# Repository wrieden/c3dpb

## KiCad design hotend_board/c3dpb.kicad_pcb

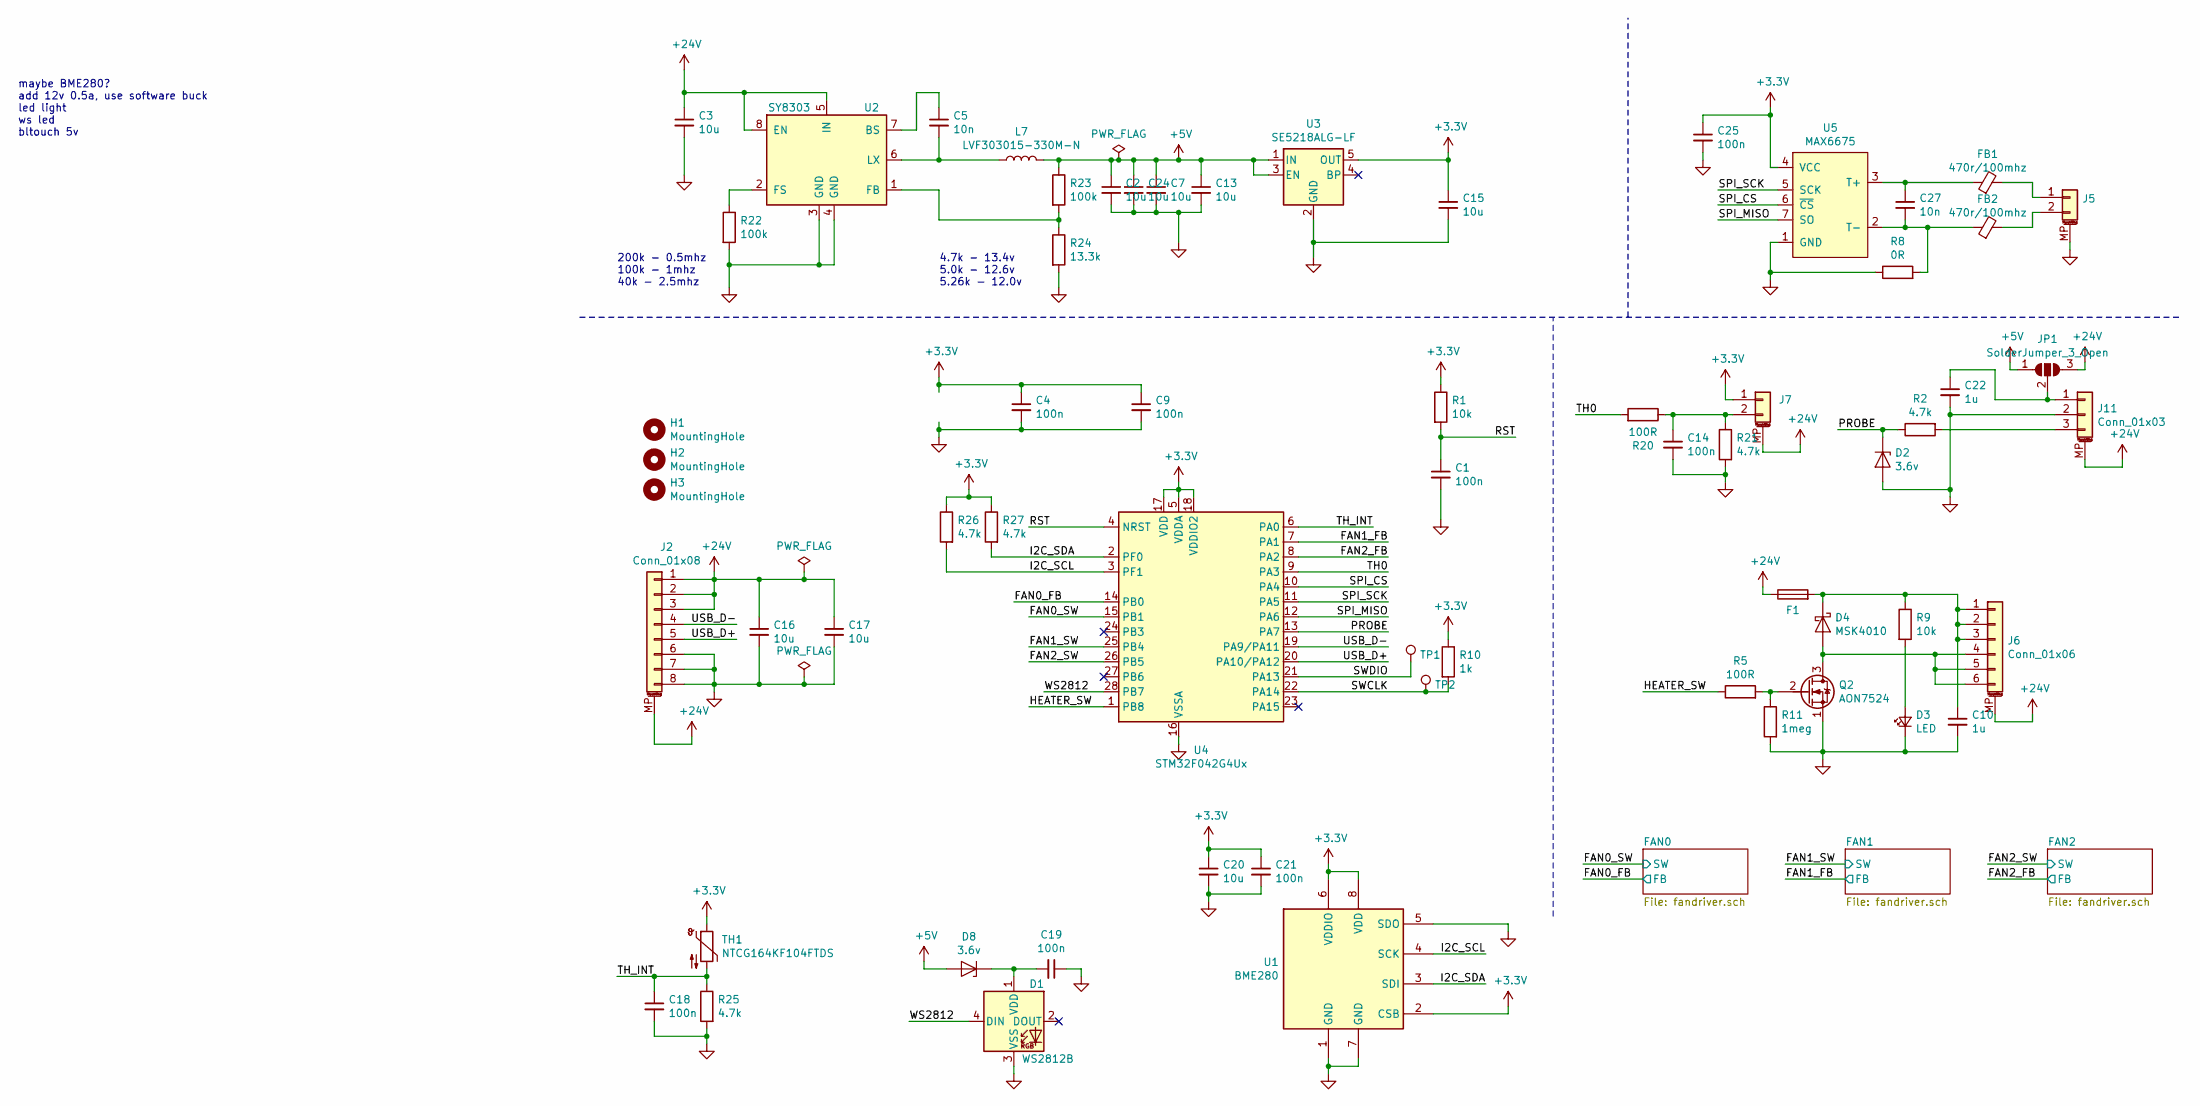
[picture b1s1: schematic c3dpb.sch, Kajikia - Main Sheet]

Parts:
C1, C4, C9, C14, C18, C19, C21, C25: 100n; 0603_CAP
C2, C7, C13, C15, C20, C24: 10u; 0603_CAP
C3, C16, C17: 10u; 1210_CAP
C5, C27: 10n; 0603_CAP
C10, C22: 1u; 0603_CAP
D1: WS2812B; WS2812B-MINI
D2, D8: 3.6v; 0603_DIODE
D3: LED; 0603_LED
D4: MSK4010; SOD-523_DIODE
F1: Fuse; 1206_RES
FB1, FB2: 470r/100mhz; 0603_IND
H1, H2: MountingHole; MountingHole_2.2mm_M2_ISO7380
H3: MountingHole; MountingHole_4.3mm_M4_ISO14580
J2: Conn_01x08; JST_SH_BM08B-SRSS-TB_1x08-1MP_P1.00mm_Vertical
J5, J7: Conn_01x02; JST_SH_BM02B-SRSS-TB_1x02-1MP_P1.00mm_Vertical
J6: Conn_01x06; JST_SH_BM06B-SRSS-TB_1x06-1MP_P1.00mm_Vertical
J11: Conn_01x03; JST_SH_BM03B-SRSS-TB_1x03-1MP_P1.00mm_Vertical
JP1: SolderJumper_3_Open; Solder Jumper 3P
L7: LVF303015-330M-N; 3x3mm_IND
Q2: AON7524; DFN3x3A_8L_EP1_P
R1, R9: 10k; 0603_RES
R2, R21, R25, R26, R27: 4.7k; 0603_RES
R5, R20: 100R; 0603_RES
R8: 0R; 0603_RES
R10: 1k; 0603_RES
R11: 1meg; 0603_RES
R22, R23: 100k; 0603_RES
R24: 13.3k; 0603_RES
TH1: NTCG164KF104FTDS; 0603_RES
TP1, TP2: TestPoint; TestPoint_Pad_D1.0mm
U1: BME280; Bosch_LGA-8_2.5x2.5mm_P0.65mm_ClockwisePinNumbering
U2: SY8303; TSOT-23-8
U3: SE5218ALG-LF; SOT-23-5
U4: STM32F042G4Ux; QFN-28_4x4mm_P0.5mm
U5: MAX6675; SO-8

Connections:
+3V3: C4.1, C9.1, C15.1, C20.1, C21.1, C25.1, J7.1, R1.1, R10.1, R26.1, R27.1, TH1.1, U1.2 (CSB), U1.6 (VDDIO), U1.8 (VDD), U3.5 (OUT), U4.5 (VDDA), U4.17 (VDD), U4.18 (VDDIO2), U5.4 (VCC)
+5V: C2.1, C7.1, C13.1, C24.1, D8.2 (A), JP1.1 (A), L7.2, R23.1, U3.1 (IN), U3.3 (EN)
+24V: C3.1, C16.1, C17.1, F1.1, J2.1, J2.2, J2.3, J2.MP (MountPin), J6.MP (MountPin), J7.MP (MountPin), J11.MP (MountPin), JP1.3 (B), U2.5 (IN), U2.8 (EN); also elsewhere on the board
/FAN0_FB: U4.14 (PB0); also elsewhere on the board
/FAN0_SW: U4.15 (PB1); also elsewhere on the board
/FAN1_FB: U4.7 (PA1); also elsewhere on the board
/FAN1_SW: U4.25 (PB4); also elsewhere on the board
/FAN2_FB: U4.8 (PA2); also elsewhere on the board
/FAN2_SW: U4.26 (PB5); also elsewhere on the board
/HEATER_SW: R5.1, U4.1 (PB8)
/I2C_SCL: R26.2, U1.4 (SCK), U4.3 (PF1)
/I2C_SDA: R27.2, U1.3 (SDI), U4.2 (PF0)
/PROBE: D2.1 (K), R2.1, U4.13 (PA7)
/RST: C1.1, R1.2, U4.4 (NRST)
/SPI_CS: U4.10 (PA4), U5.6 (~CS)
/SPI_MISO: U4.12 (PA6), U5.7 (SO)
/SPI_SCK: U4.11 (PA5), U5.5 (SCK)
/SWCLK: R10.2, TP2.1, U4.22 (PA14)
/SWDIO: TP1.1, U4.21 (PA13)
/TH0: R20.2, U4.9 (PA3)
/TH_INT: C18.1, R25.1, TH1.2, U4.6 (PA0)
/USB_D+: J2.5, U4.20 (PA10/PA12)
/USB_D-: J2.4, U4.19 (PA9/PA11)
/WS2812: D1.4 (DIN), U4.28 (PB7)
GND: C1.2, C2.2, C3.2, C4.2, C7.2, C9.2, C10.2, C13.2, C14.2, C15.2, C16.2, C17.2, C18.2, C19.1, C20.2, C21.2, C22.2, C24.2, C25.2, D1.3 (VSS), D2.2 (A), D3.1 (K), J2.6, J2.7, J2.8, J5.MP (MountPin), J11.2, Q2.1 (S), R8.1, R11.2, R21.2, R22.2, R24.2, R25.2, U1.1 (GND), U1.5 (SDO), U1.7 (GND), U2.3 (GND), U2.4 (GND), U3.2 (GND), U4.16 (VSSA), U5.1 (GND); also elsewhere on the board
unnamed: C5.1, U2.7 (BS)
unnamed: C5.2, L7.1, U2.6 (LX)
unnamed: C10.1, D4.1 (K), F1.2, J6.1, J6.2, J6.3, R9.1
unnamed: C14.1, J7.2, R20.1, R21.1
unnamed: C19.2, D1.1 (VDD), D8.1 (K)
unnamed: C22.1, J11.1, JP1.2 (C)
unnamed: C27.1, FB1.1, U5.3 (T+)
unnamed: C27.2, FB2.1, R8.2, U5.2 (T-)
unnamed: D3.2 (A), R9.2
unnamed: D4.2 (A), J6.4, J6.5, J6.6, Q2.3 (D)
unnamed: FB1.2, J5.1
unnamed: FB2.2, J5.2
unnamed: J11.3, R2.2
unnamed: Q2.2 (G), R5.2, R11.1
unnamed: R22.1, U2.2 (FS)
unnamed: R23.2, R24.1, U2.1 (FB)

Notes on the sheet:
maybe BME280? add 12v 0.5a, use software buck led light ws led bltouch 5v
4.7k - 13.4v 5.0k - 12.6v 5.26k - 12.0v
200k - 0.5mhz 100k - 1mhz 40k - 2.5mhz

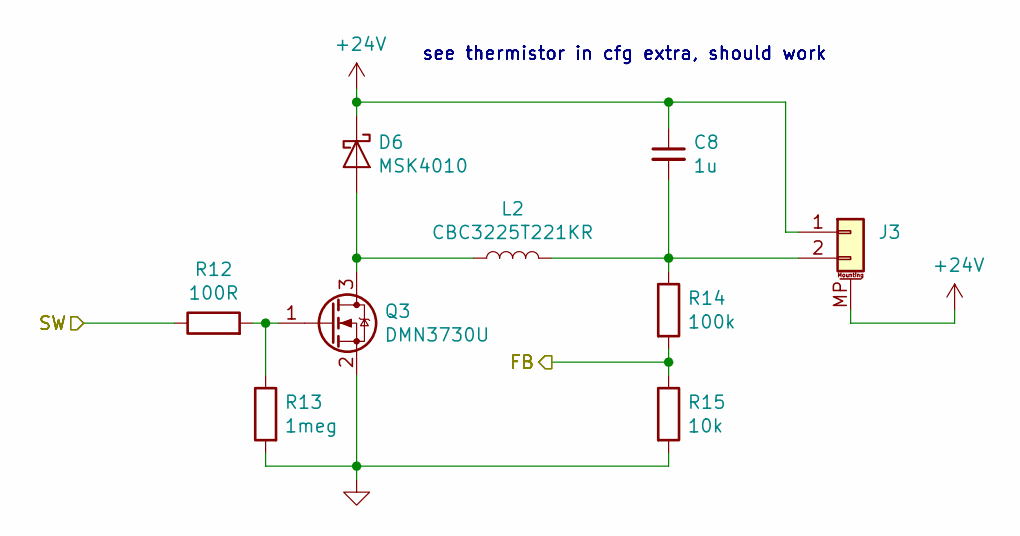
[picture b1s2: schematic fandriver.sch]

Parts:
C6: 1u; 0603_CAP
D5: MSK4010; SOD-523_DIODE
J1: Conn_01x02; JST_SH_BM02B-SRSS-TB_1x02-1MP_P1.00mm_Vertical
L1: CBC3225T221KR; 1210_CAP
Q1: DMN3730U; SOT-23
R3: 100R; 0603_RES
R4: 1meg; 0603_RES
R6: 100k; 0603_RES
R7: 10k; 0603_RES

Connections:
+24V: C6.1, D5.1 (K), J1.1, J1.MP (MountPin); also elsewhere on the board
/FAN0_FB: R6.2, R7.1; also elsewhere on the board
/FAN0_SW: R3.1; also elsewhere on the board
GND: Q1.2 (S), R4.2, R7.2; also elsewhere on the board
unnamed: C6.2, J1.2, L1.2, R6.1
unnamed: D5.2 (A), L1.1, Q1.3 (D)
unnamed: Q1.1 (G), R3.2, R4.1

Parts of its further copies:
C8, C11: 1u; 0603_CAP
D6, D7: MSK4010; SOD-523_DIODE
J3, J4: Conn_01x02; JST_SH_BM02B-SRSS-TB_1x02-1MP_P1.00mm_Vertical
L2, L3: CBC3225T221KR; 1210_CAP
Q3, Q4: DMN3730U; SOT-23
R12, R16: 100R; 0603_RES
R13, R17: 1meg; 0603_RES
R14, R18: 100k; 0603_RES
R15, R19: 10k; 0603_RES

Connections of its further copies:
+24V: C8.1, C11.1, D6.1 (K), D7.1 (K), J3.1, J3.MP (MountPin), J4.1, J4.MP (MountPin); also elsewhere on the board
/FAN1_FB: R14.2, R15.1; also elsewhere on the board
/FAN1_SW: R12.1; also elsewhere on the board
/FAN2_FB: R18.2, R19.1; also elsewhere on the board
/FAN2_SW: R16.1; also elsewhere on the board
GND: Q3.2 (S), Q4.2 (S), R13.2, R15.2, R17.2, R19.2; also elsewhere on the board
unnamed: C8.2, J3.2, L2.2, R14.1
unnamed: C11.2, J4.2, L3.2, R18.1
unnamed: D6.2 (A), L2.1, Q3.3 (D)
unnamed: D7.2 (A), L3.1, Q4.3 (D)
unnamed: Q3.1 (G), R12.2, R13.1
unnamed: Q4.1 (G), R16.2, R17.1

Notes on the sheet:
see thermistor in cfg extra, should work

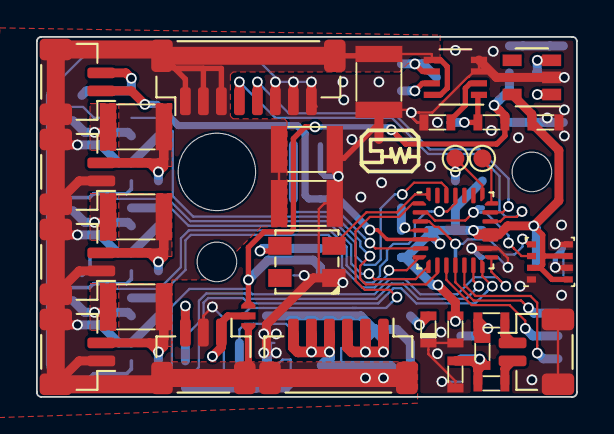
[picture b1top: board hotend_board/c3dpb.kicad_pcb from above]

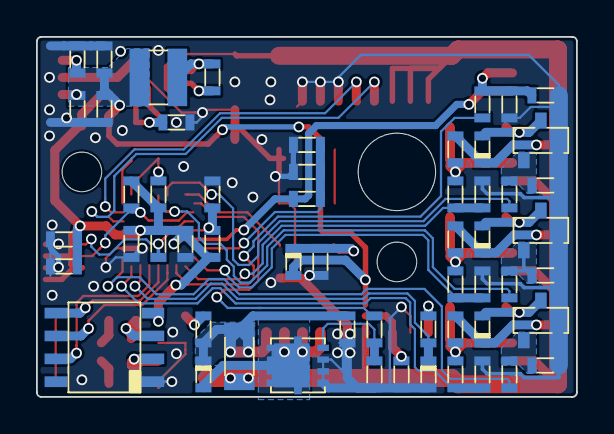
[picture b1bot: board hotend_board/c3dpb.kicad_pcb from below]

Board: 2 copper layers, 30.0 x 20.0 mm, 90 parts (56 on the bottom side), 50 nets.

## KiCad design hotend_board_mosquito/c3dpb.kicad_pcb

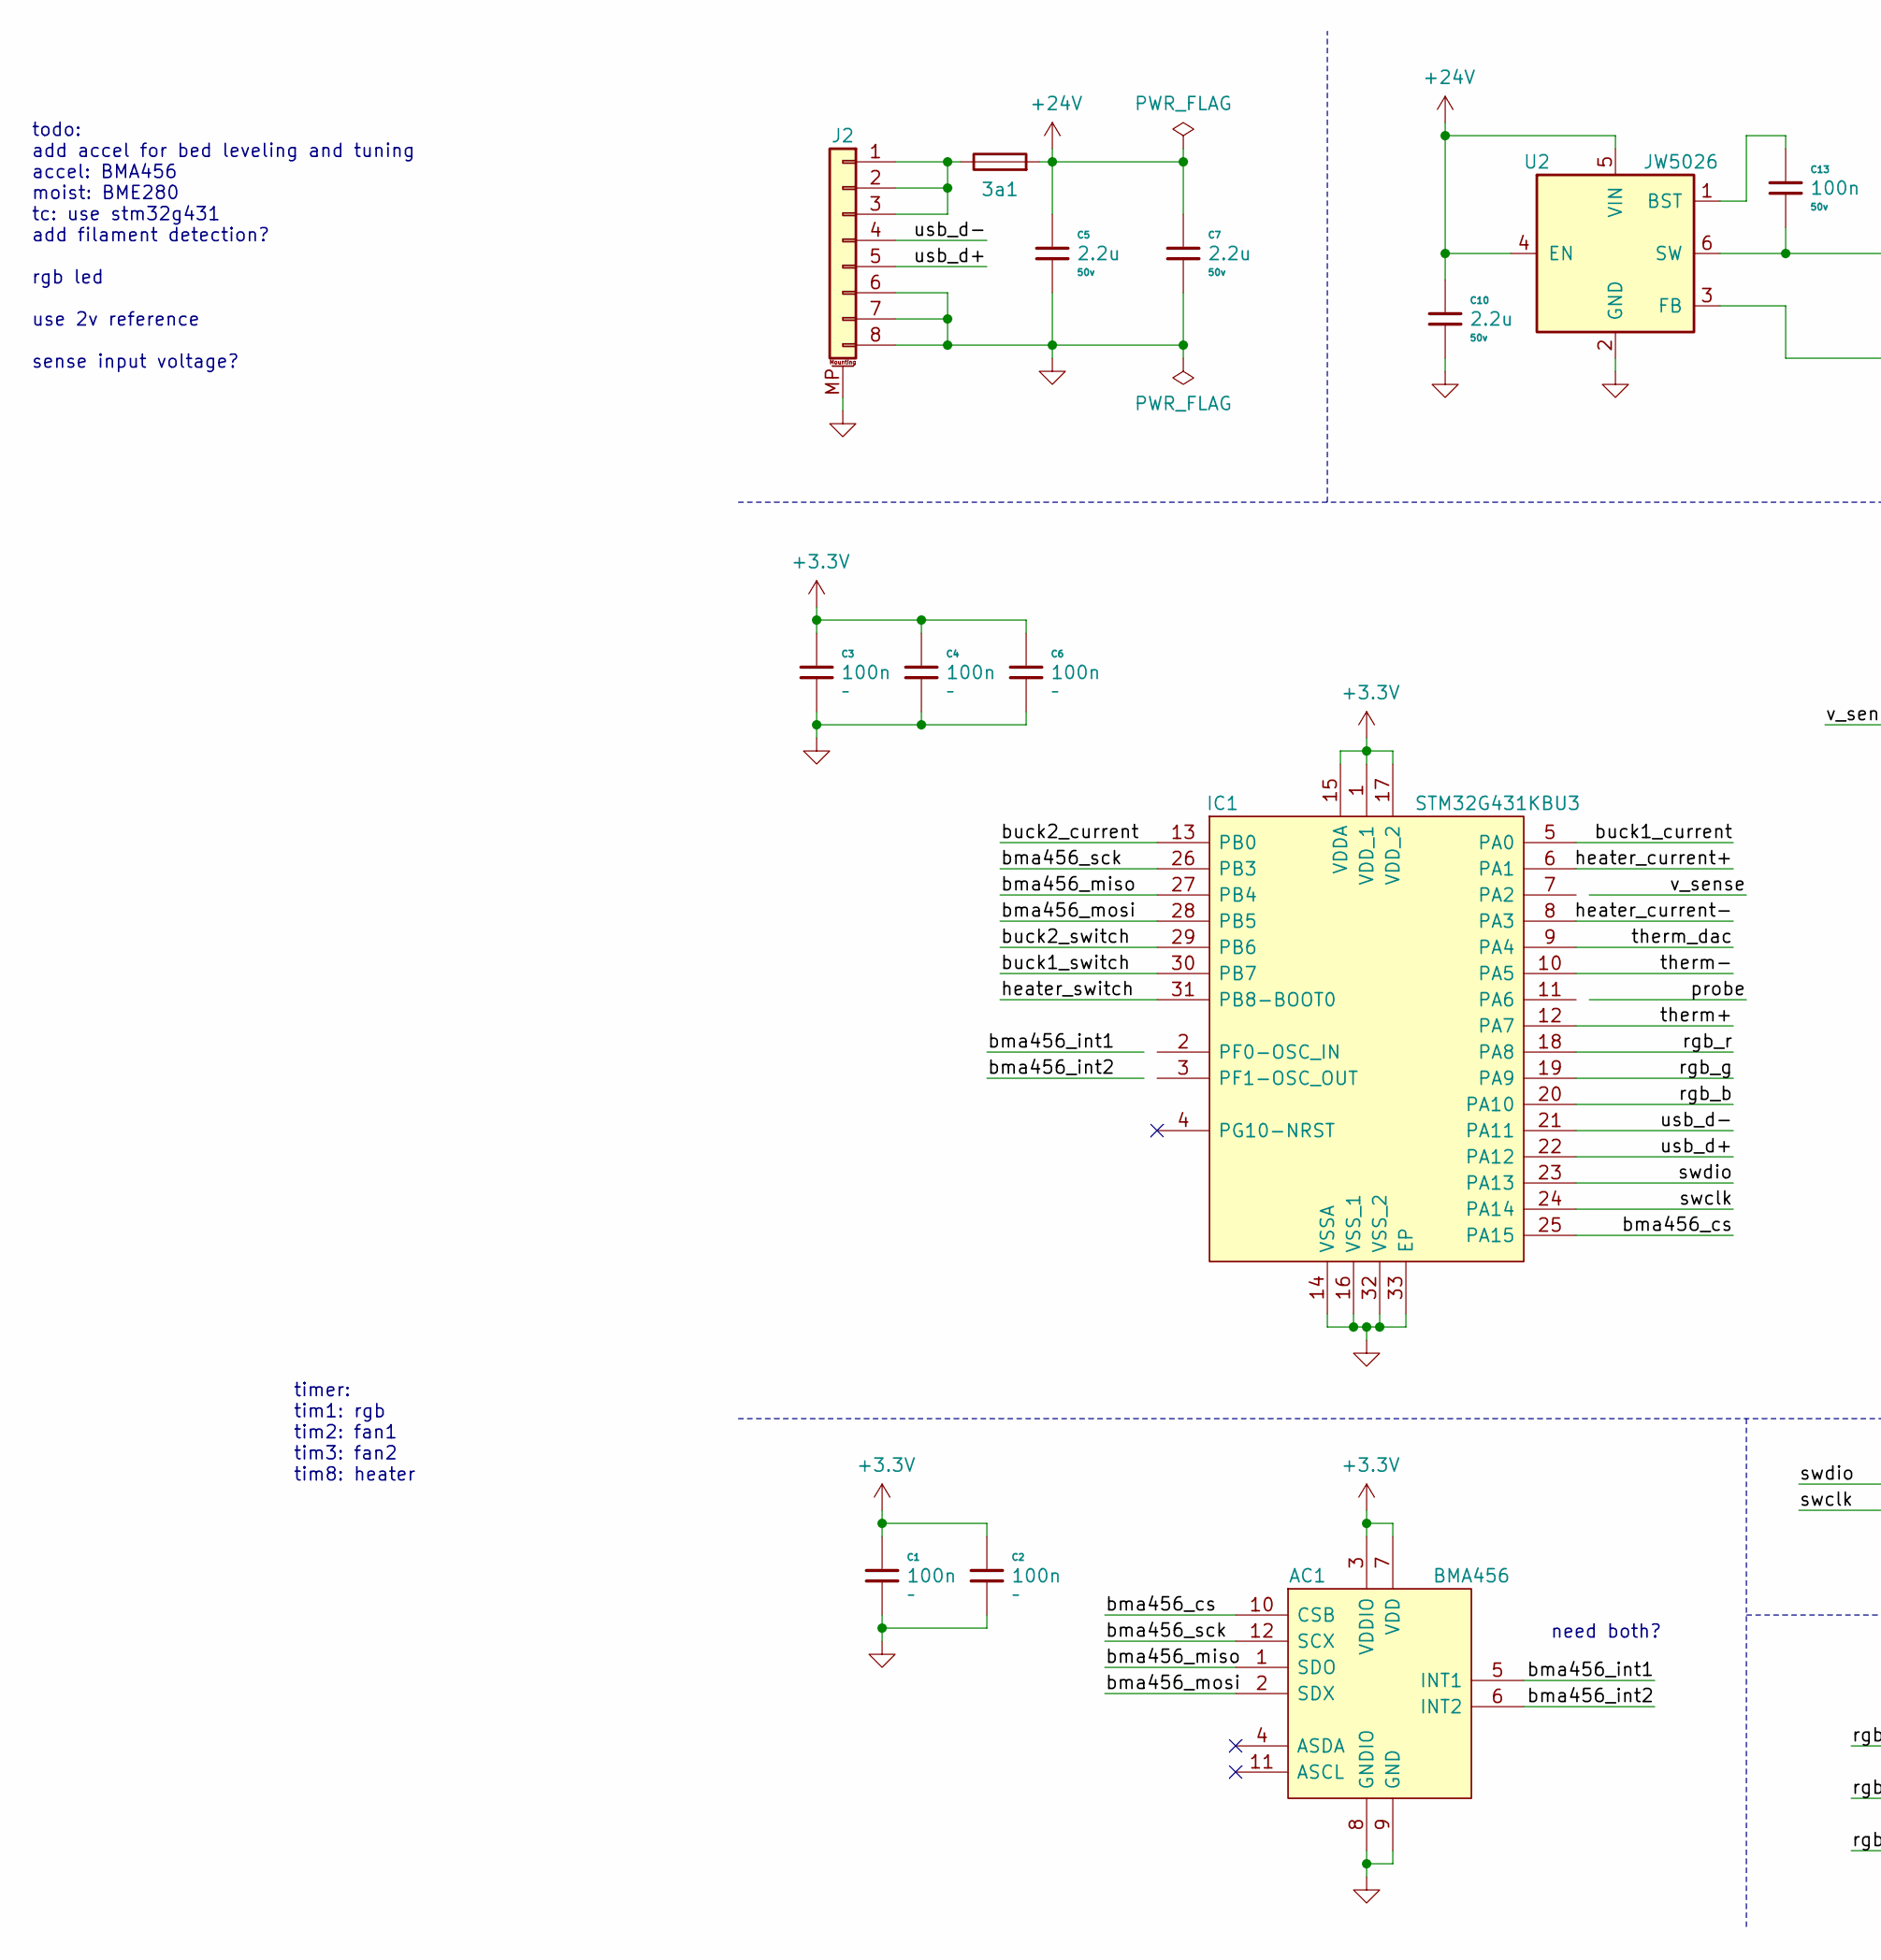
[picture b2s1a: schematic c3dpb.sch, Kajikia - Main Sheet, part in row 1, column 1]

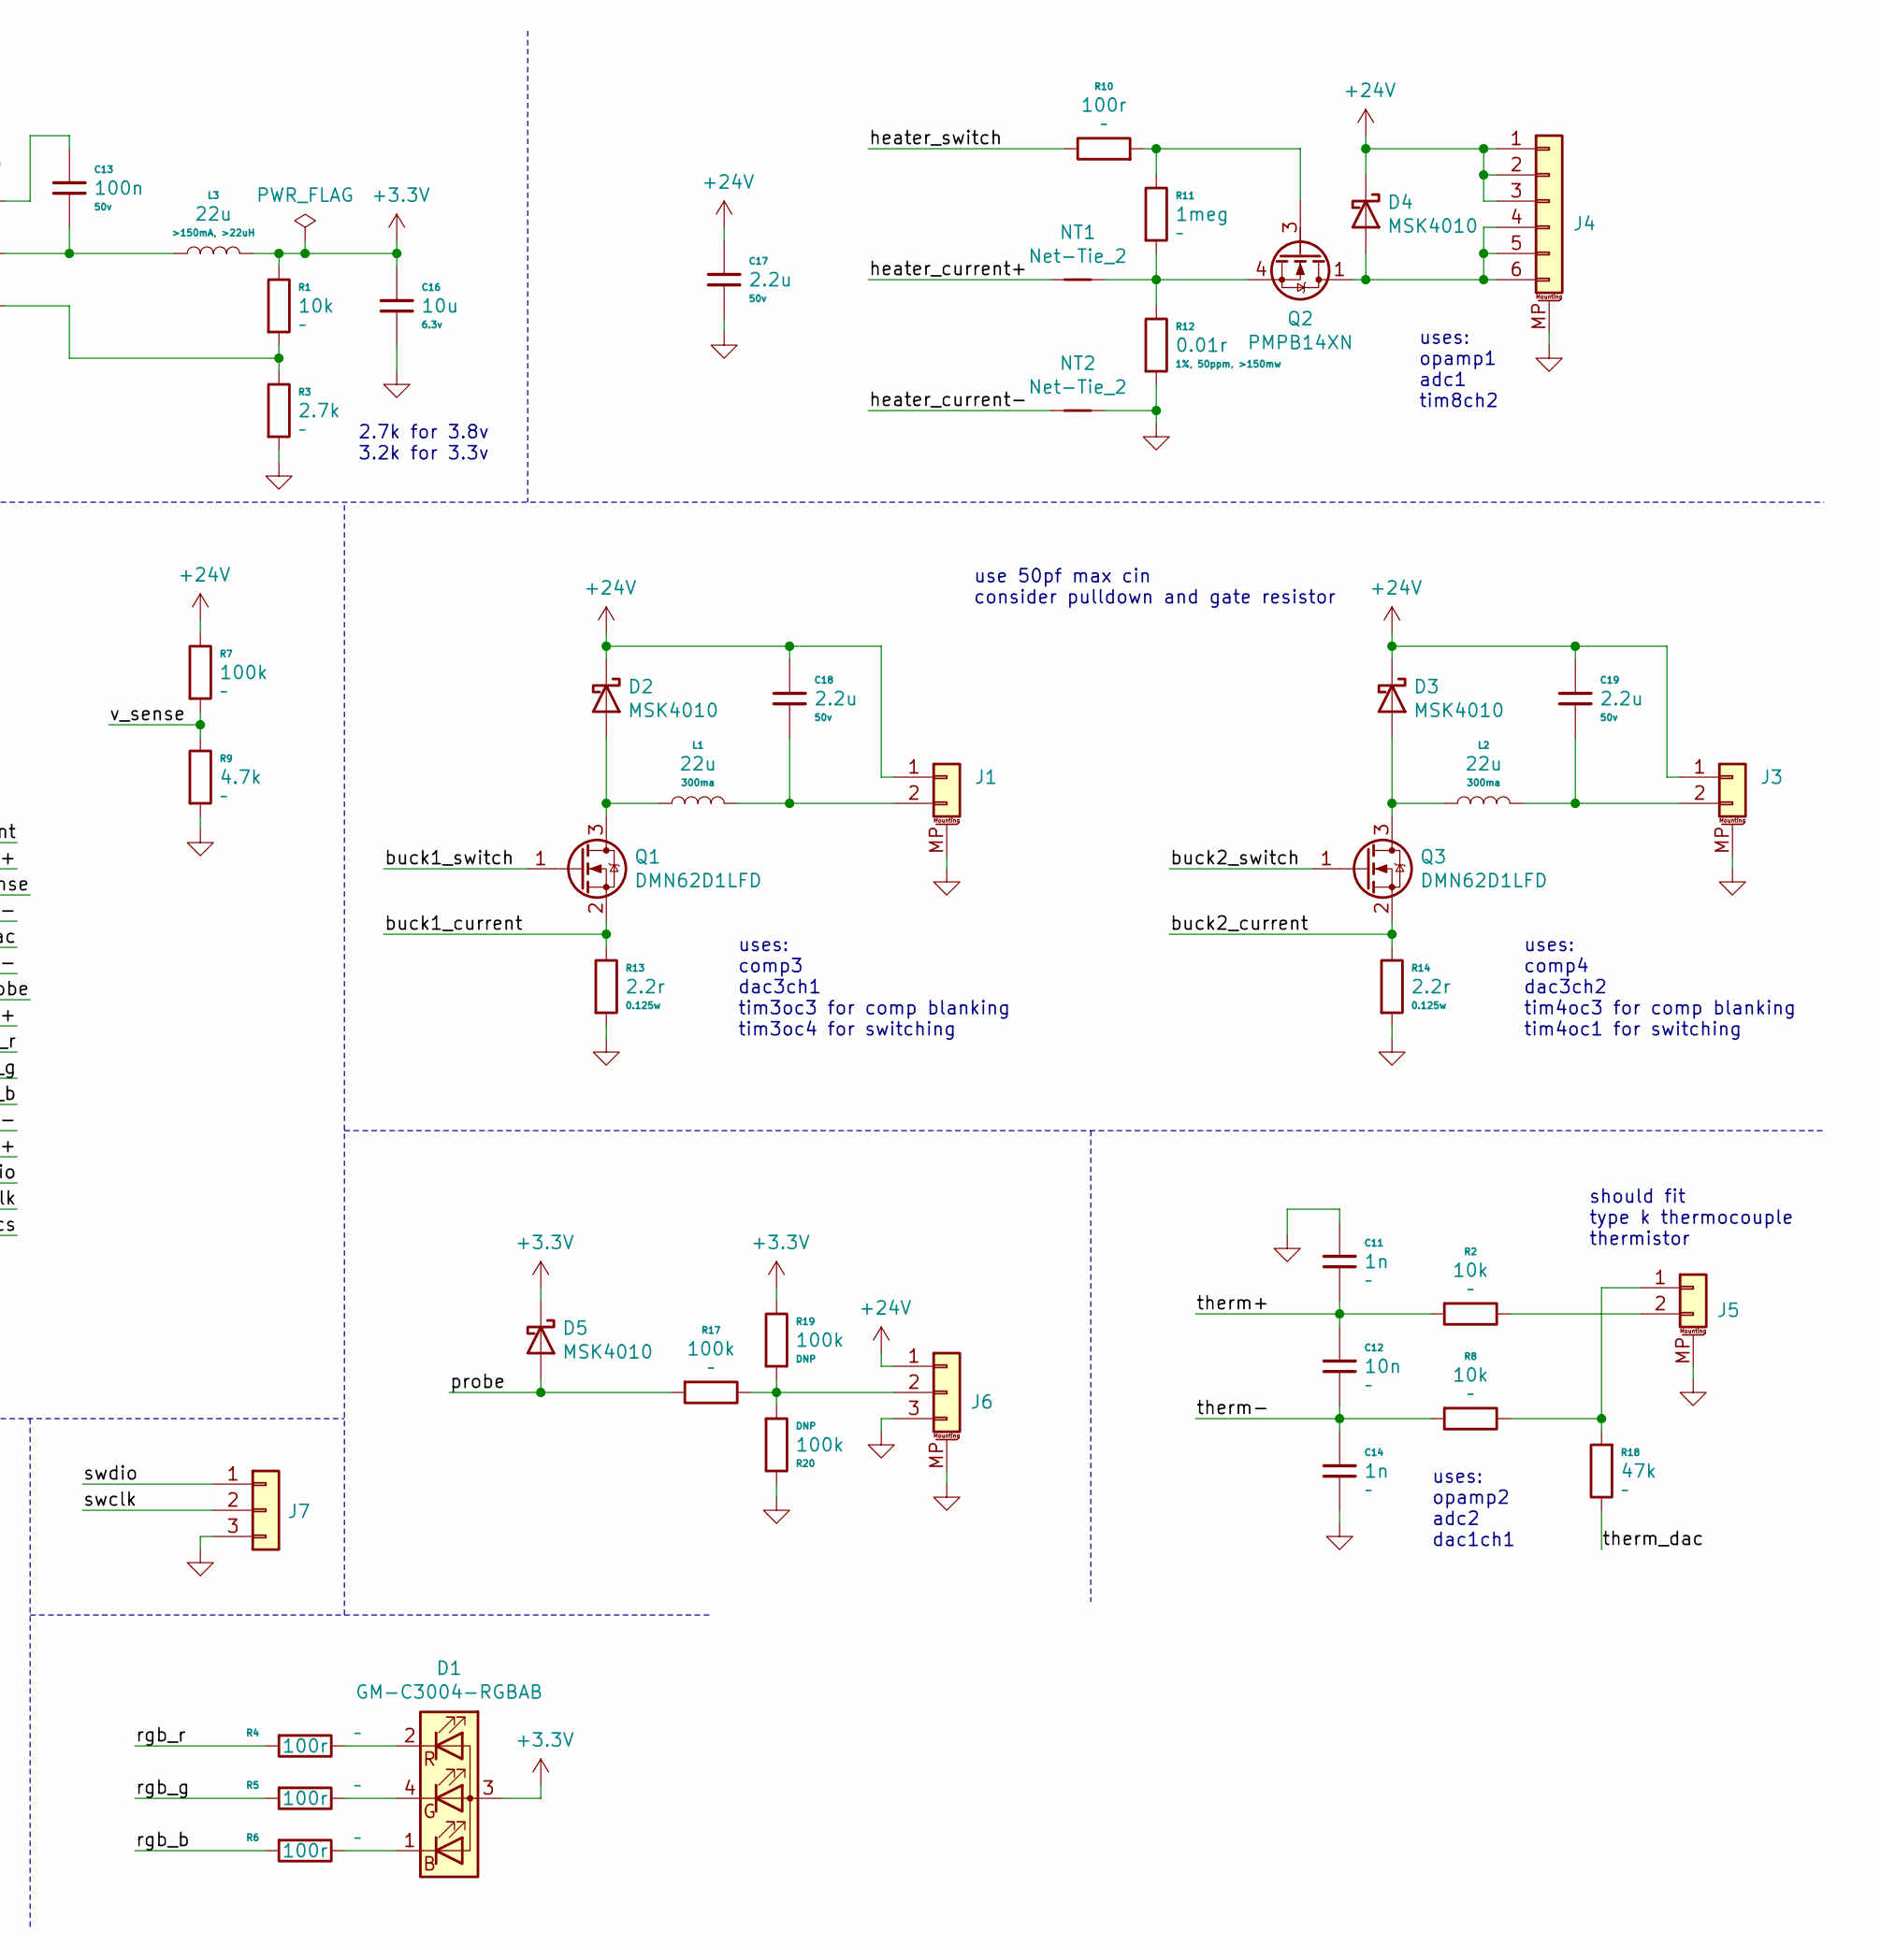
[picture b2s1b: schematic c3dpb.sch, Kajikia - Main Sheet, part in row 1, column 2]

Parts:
3a1: Fuse; 1206_RES
AC1: BMA456; BOSCH_LGA-12
C1, C2, C3, C4, C6, C13: 100n; 0402_CAP
C5, C7, C10, C17, C18, C19: 2.2u; 0603_CAP
C11, C14: 1n; 0402_CAP
C12: 10n; 0402_CAP
C16: 10u; 0402_CAP
D1: GM-C3004-RGBAB
D2, D3, D4, D5: MSK4010; SOD-523_DIODE
IC1: STM32G431KBU3; QFN-32-1EP_5x5mm_P0.5mm_EP3.6x3.6mm
J1, J3: Conn_01x02; JST_SH_BM02B-SRSS-TB_1x02-1MP_P1.00mm_Vertical
J2: Conn_01x08; JST_SH_BM08B-SRSS-TB_1x08-1MP_P1.00mm_Vertical
J4: Conn_01x06_MountingPin; JST_SH_BM06B-SRSS-TB_1x06-1MP_P1.00mm_Vertical
J5: Conn_01x02_MountingPin; JST_SH_BM02B-SRSS-TB_1x02-1MP_P1.00mm_Vertical
J6: Conn_01x03_MountingPin; JST_SH_BM03B-SRSS-TB_1x03-1MP_P1.00mm_Vertical
J7: Conn_01x03; pads_3x1mm
L1, L2, L3: 22u; 0805_IND
NT1, NT2: Net-Tie_2; nettie-1.27
Q1, Q3: DMN62D1LFD; U-DFN1212-3
Q2: PMPB14XN; Diodes_UDFN2020-6_Type-F
R1, R2, R8: 10k; 0402_RES
R3: 2.7k; 0402_RES
R4, R5, R6, R10: 100r; 0402_RES
R7, R17, R19, R20: 100k; 0402_RES
R9: 4.7k; 0402_RES
R11: 1meg; 0402_RES
R12: 0.01r; 0603_RES
R13, R14: 2.2r; 0603_RES
R18: 47k; 0402_RES
U2: JW5026; SOT-23-6

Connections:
+3V3: AC1.3 (VDDIO), AC1.7 (VDD), C1.1, C2.1, C3.1, C4.1, C6.1, C16.1, D1.3 (A), D5.1 (K), IC1.1 (VDD_1), IC1.15 (VDDA), IC1.17 (VDD_2), L3.2, R1.1, R19.1
+24V: 3a1.2, C5.1, C7.1, C10.1, C17.1, C18.1, C19.1, D2.1 (K), D3.1 (K), D4.1 (K), J1.1, J3.1, J4.1, J4.2, J4.3, J6.1, R7.1, U2.4 (EN), U2.5 (VIN)
/bma456_cs: AC1.10 (CSB), IC1.25 (PA15)
/bma456_int1: AC1.5 (INT1)
/bma456_int2: AC1.6 (INT2)
/bma456_miso: AC1.1 (SDO), IC1.27 (PB4)
/bma456_mosi: AC1.2 (SDX), IC1.28 (PB5)
/bma456_sck: AC1.12 (SCX), IC1.26 (PB3)
/buck1_current: IC1.5 (PA0), Q1.2 (S), R13.1
/buck1_switch: IC1.30 (PB7), Q1.1 (G)
/buck2_current: IC1.13 (PB0), Q3.2 (S), R14.1
/buck2_switch: IC1.29 (PB6), Q3.1 (G)
/heater_current+: IC1.6 (PA1), NT1.2
/heater_current-: IC1.8 (PA3), NT2.2
/heater_switch: IC1.31 (PB8-BOOT0), R10.1
/probe: D5.2 (A), R17.2
/rgb_b: IC1.20 (PA10), R6.2
/rgb_g: IC1.19 (PA9), R5.2
/rgb_r: IC1.18 (PA8), R4.2
/swclk: IC1.24 (PA14), J7.2
/swdio: IC1.23 (PA13), J7.1
/therm+: C11.2, C12.1, IC1.12 (PA7), R2.2
/therm-: C12.2, C14.1, IC1.10 (PA5), R8.2
/therm_dac: IC1.9 (PA4), R18.1
/usb_d+: IC1.22 (PA12), J2.5
/usb_d-: IC1.21 (PA11), J2.4
/v_sense: R7.2, R9.1
GND: AC1.8 (GNDIO), AC1.9 (GND), C1.2, C2.2, C3.2, C4.2, C5.2, C6.2, C7.2, C10.2, C11.1, C14.2, C16.2, C17.2, IC1.14 (VSSA), IC1.16 (VSS_1), IC1.32 (VSS_2), IC1.33 (EP), J1.MP (MountPin), J2.6, J2.7, J2.8, J2.MP (MountPin), J3.MP (MountPin), J4.MP (MountPin), J5.MP (MountPin), J6.3, J6.MP (MountPin), J7.3, NT2.1, R3.2, R9.2, R12.2, R13.2, R14.2, R20.1, U2.2 (GND)
unnamed: 3a1.1, J2.1, J2.2, J2.3
unnamed: C13.1, U2.1 (BST)
unnamed: C13.2, L3.1, U2.6 (SW)
unnamed: C18.2, J1.2, L1.2
unnamed: C19.2, J3.2, L2.2
unnamed: D1.1 (BK), R6.1
unnamed: D1.2 (RK), R4.1
unnamed: D1.4 (GK), R5.1
unnamed: D2.2 (A), L1.1, Q1.3 (D)
unnamed: D3.2 (A), L2.1, Q3.3 (D)
unnamed: D4.2 (A), J4.4, J4.5, J4.6, Q2.1 (D), Q2.2 (D), Q2.5 (D), Q2.6 (D), Q2.7 (D)
unnamed: J5.1, R8.1, R18.2
unnamed: J5.2, R2.1
unnamed: J6.2, R17.1, R19.2, R20.2
unnamed: NT1.1, Q2.4 (S), Q2.8 (S), R11.2, R12.1
unnamed: Q2.3 (G), R10.2, R11.1
unnamed: R1.2, R3.1, U2.3 (FB)

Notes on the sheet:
todo: add accel for bed leveling and tuning accel: BMA456 moist: BME280 tc: use stm32g431 add filament detection? rgb led use 2v reference sense input voltage?
timer: tim1: rgb tim2: fan1 tim3: fan2 tim8: heater
should fit type k thermocouple thermistor
need both?
use 50pf max cin consider pulldown and gate resistor
uses: comp4 dac3ch2 tim4oc3 for comp blanking tim4oc1 for switching
uses: comp3 dac3ch1 tim3oc3 for comp blanking tim3oc4 for switching
uses: opamp2 adc2 dac1ch1
uses: opamp1 adc1 tim8ch2
2.7k for 3.8v 3.2k for 3.3v

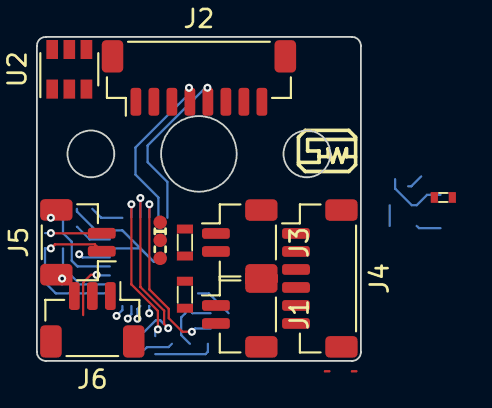
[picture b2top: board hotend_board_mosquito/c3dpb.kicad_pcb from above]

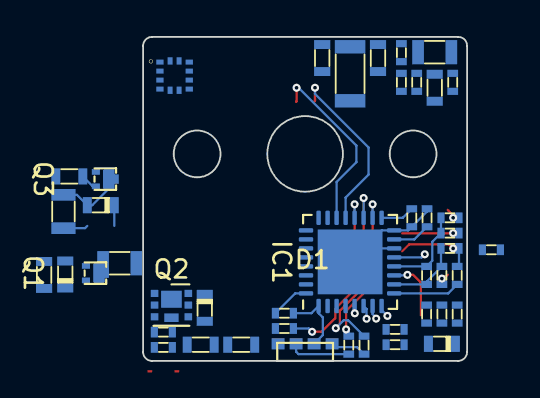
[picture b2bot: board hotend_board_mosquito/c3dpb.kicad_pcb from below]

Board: 4 copper layers, 18.0 x 18.0 mm, 58 parts (45 on the bottom side), 43 nets.
